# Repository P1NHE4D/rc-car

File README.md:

# RC Car Project
This repository contains all files for the controller boards I designed for a RC car I am building myself.

## Version 1
The first version of the board uses a AtMega 328 MCU for controlling the motor driver, lights, and steering of the car. It is connected to an external
ESP 8266 chip for enabling wireless communication.

<div align="center">

</div>

## Version 2
The second version is currently in development. It replaces the AtMega 328 chip with an on-board ESP32 in order to reduce the overall footprint
of the chip. It also features a USB-C connector to facilitate flashing and debugging the controller without having to rely on additional 
debugging equipment.

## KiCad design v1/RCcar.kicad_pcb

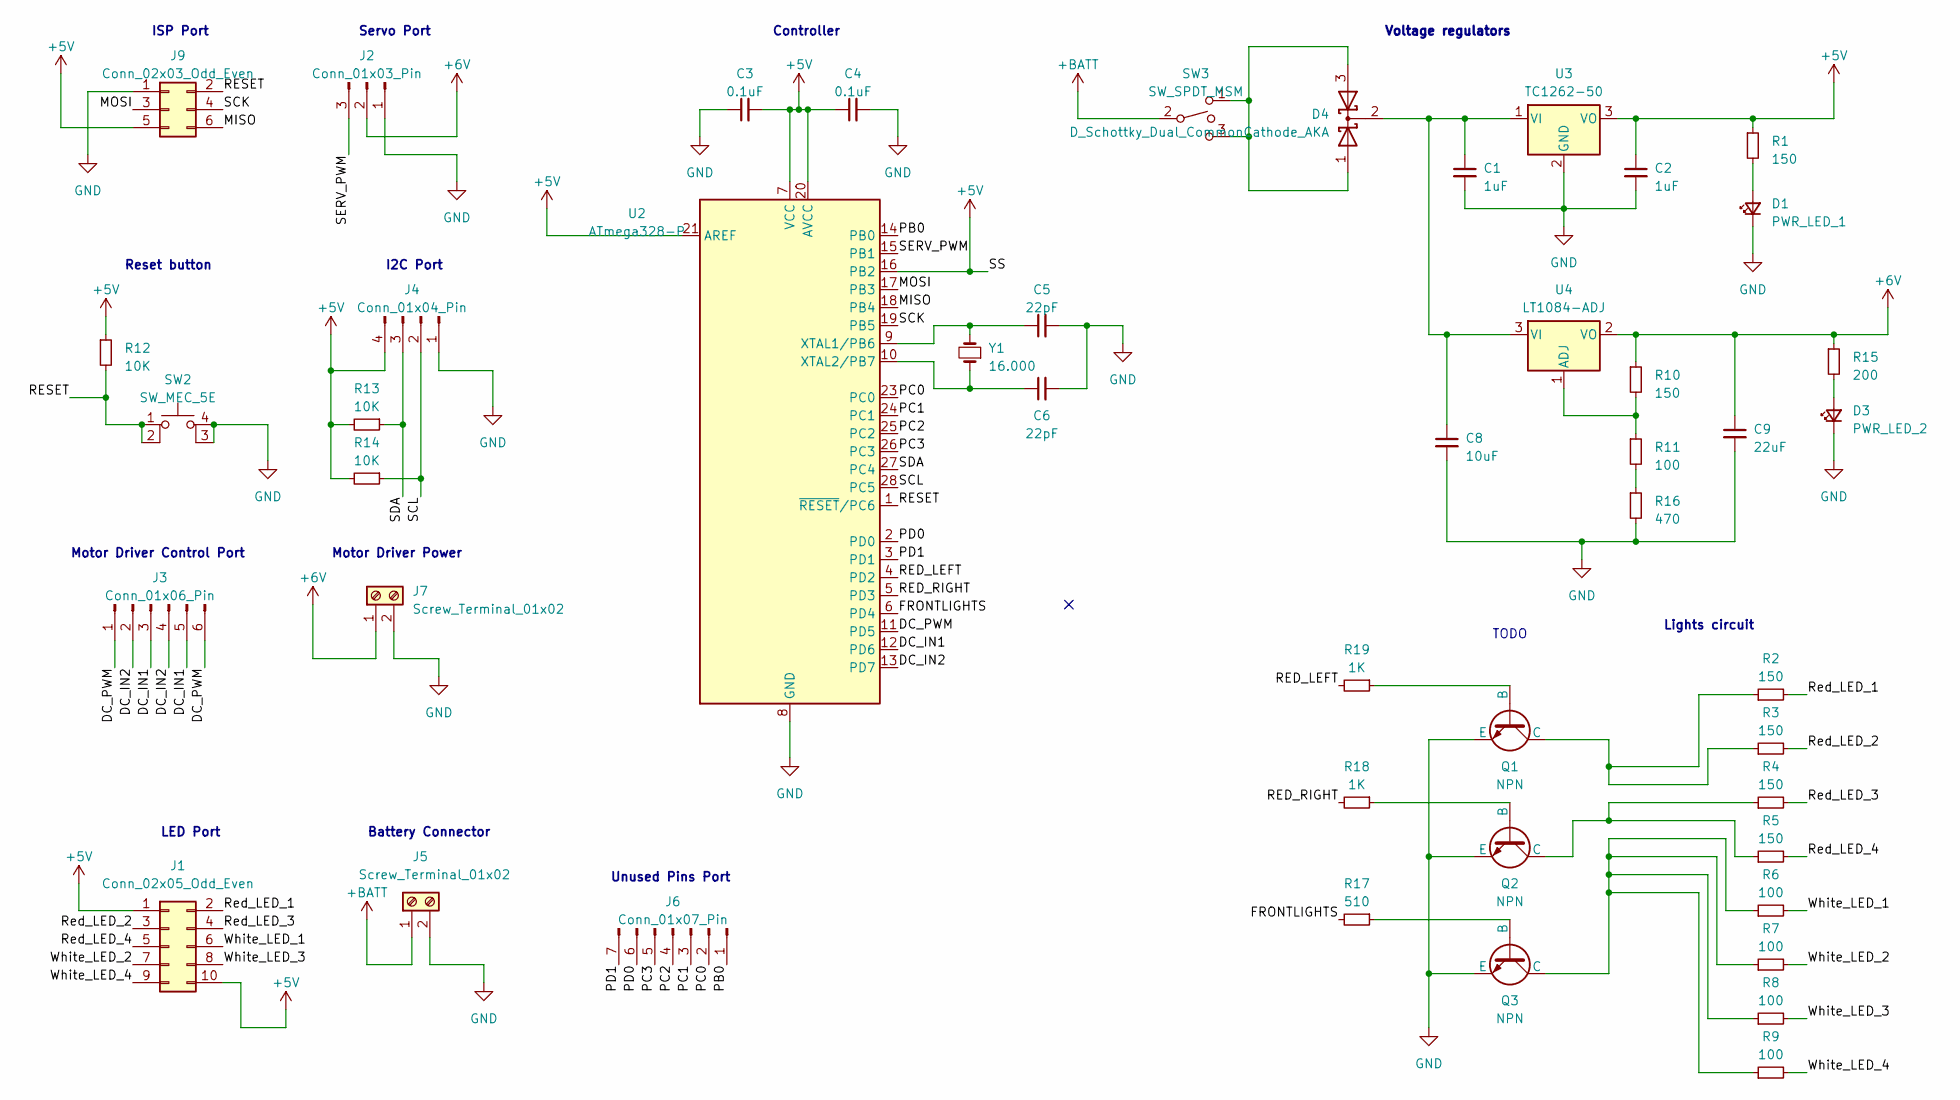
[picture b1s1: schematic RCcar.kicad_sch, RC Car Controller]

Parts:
C1, C2: 1uF; C_1206_3216Metric_Pad1.33x1.80mm_HandSolder
C3, C4: 0.1uF; C_1206_3216Metric_Pad1.33x1.80mm_HandSolder
C5, C6: 22pF; C_1206_3216Metric_Pad1.33x1.80mm_HandSolder
C8: 10uF; C_1206_3216Metric_Pad1.33x1.80mm_HandSolder
C9: 22uF; C_1206_3216Metric_Pad1.33x1.80mm_HandSolder
D1: PWR_LED_1; LED_1206_3216Metric_Pad1.42x1.75mm_HandSolder
D3: PWR_LED_2; LED_1206_3216Metric_Pad1.42x1.75mm_HandSolder
D4: D_Schottky_Dual_CommonCathode_AKA; TO-252-2
J1: Conn_02x05_Odd_Even; PinHeader_2x05_P2.54mm_Vertical
J2: Conn_01x03_Pin; PinHeader_1x03_P2.54mm_Vertical
J3: Conn_01x06_Pin; PinHeader_1x06_P2.54mm_Vertical
J4: Conn_01x04_Pin; PinHeader_1x04_P2.54mm_Vertical
J5, J7: Screw_Terminal_01x02; CTB0700-2
J6: Conn_01x07_Pin; PinHeader_1x07_P2.54mm_Vertical
J9: Conn_02x03_Odd_Even; PinHeader_2x03_P2.54mm_Vertical
Q1, Q2, Q3: NPN; SOT-23
R1, R2, R3, R4, R5, R10: 150; R_1206_3216Metric_Pad1.30x1.75mm_HandSolder
R6, R7, R8, R9, R11: 100; R_1206_3216Metric_Pad1.30x1.75mm_HandSolder
R12, R13, R14: 10K; R_1206_3216Metric_Pad1.30x1.75mm_HandSolder
R15: 200; R_1206_3216Metric_Pad1.30x1.75mm_HandSolder
R16: 470; R_1206_3216Metric_Pad1.30x1.75mm_HandSolder
R17: 510; R_1206_3216Metric_Pad1.30x1.75mm_HandSolder
R18, R19: 1K; R_1206_3216Metric_Pad1.30x1.75mm_HandSolder
SW2: SW_MEC_5E; ElegooButton
SW3: SW_SPDT_MSM; 1101M2S3CQE2
U2: ATmega328-P; DIP-28_W7.62mm
U3: TC1262-50; SOT-223
U4: LT1084-ADJ; TO-252-2
Y1: 16.000; Crystal_HC49-4H_Vertical

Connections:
+5V: C2.1, C3.2, C4.1, J1.1, J1.10, J4.4, J9.5, R1.1, R12.1, R13.2, R14.2, U2.7 (VCC), U2.16 (PB2), U2.20 (AVCC), U2.21 (AREF), U3.3 (VO)
+6V: C9.1, J2.2, J7.1, R10.1, R15.1, U4.2 (VO)
+BATT: J5.1, SW3.2
/DC_IN1: J3.3, J3.5, U2.12 (PD6)
/DC_IN2: J3.2, J3.4, U2.13 (PD7)
/DC_PWM: J3.1, J3.6, U2.11 (PD5)
/FRONTLIGHTS: R17.2, U2.6 (PD4)
/MISO: J9.6, U2.18 (PB4)
/MOSI: J9.3, U2.17 (PB3)
/PB0: J6.1, U2.14 (PB0)
/PC0: J6.2, U2.23 (PC0)
/PC1: J6.3, U2.24 (PC1)
/PC2: J6.4, U2.25 (PC2)
/PC3: J6.5, U2.26 (PC3)
/PD0: J6.6, U2.2 (PD0)
/PD1: J6.7, U2.3 (PD1)
/RED_LEFT: R19.2, U2.4 (PD2)
/RED_RIGHT: R18.2, U2.5 (PD3)
/RESET: J9.2, R12.2, SW2.1, SW2.2, U2.1 (~RESET/PC6)
/Red_LED_1: J1.2, R2.2
/Red_LED_2: J1.3, R3.2
/Red_LED_3: J1.4, R4.2
/Red_LED_4: J1.5, R5.2
/SCK: J9.4, U2.19 (PB5)
/SCL: J4.2, R14.1, U2.28 (PC5)
/SDA: J4.3, R13.1, U2.27 (PC4)
/SERV_PWM: J2.3, U2.15 (PB1)
/White_LED_1: J1.6, R6.2
/White_LED_2: J1.7, R7.2
/White_LED_3: J1.8, R8.2
/White_LED_4: J1.9, R9.2
GND: C1.2, C2.2, C3.1, C4.2, C5.2, C6.2, C8.2, C9.2, D1.1 (K), D3.1 (K), J2.1, J4.1, J5.2, J7.2, J9.1, Q1.3 (E), Q2.3 (E), Q3.3 (E), R16.2, SW2.3 (K), SW2.4 (A), U2.8 (GND), U2.22 (GND), U3.2 (GND)
unnamed: D1.2 (A), R1.2
unnamed: D3.2 (A), R15.2
unnamed: D4.1 (A), D4.3 (A), SW3.1, SW3.3
unnamed: C1.1, C8.1, D4.2 (K), U3.1 (VI), U4.3 (VI)
unnamed: Q1.2 (B), R19.1
unnamed: Q1.1 (C), R2.1, R3.1
unnamed: Q2.2 (B), R18.1
unnamed: Q2.1 (C), R4.1, R5.1
unnamed: Q3.2 (B), R17.1
unnamed: Q3.1 (C), R6.1, R7.1, R8.1, R9.1
unnamed: R11.2, R16.1
unnamed: C5.1, U2.9 (XTAL1/PB6), Y1.2
unnamed: C6.1, U2.10 (XTAL2/PB7), Y1.1
unnamed: R10.2, R11.1, U4.1 (ADJ)

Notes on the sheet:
Servo Port
LED Port
Voltage regulators
Reset button
Lights circuit
TODO
Battery Connector
Motor Driver Power
Controller
ISP Port
Motor Driver Control Port
I2C Port
Unused Pins Port

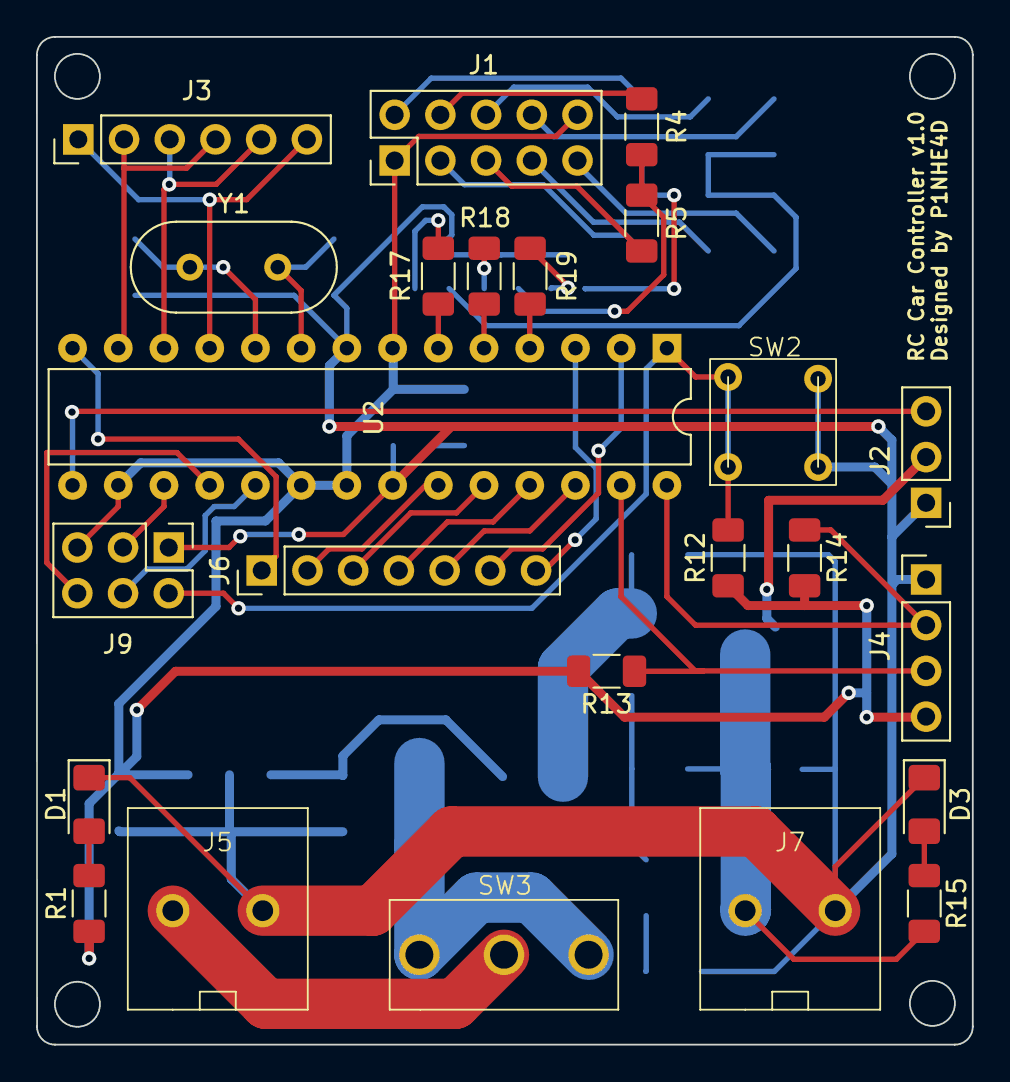
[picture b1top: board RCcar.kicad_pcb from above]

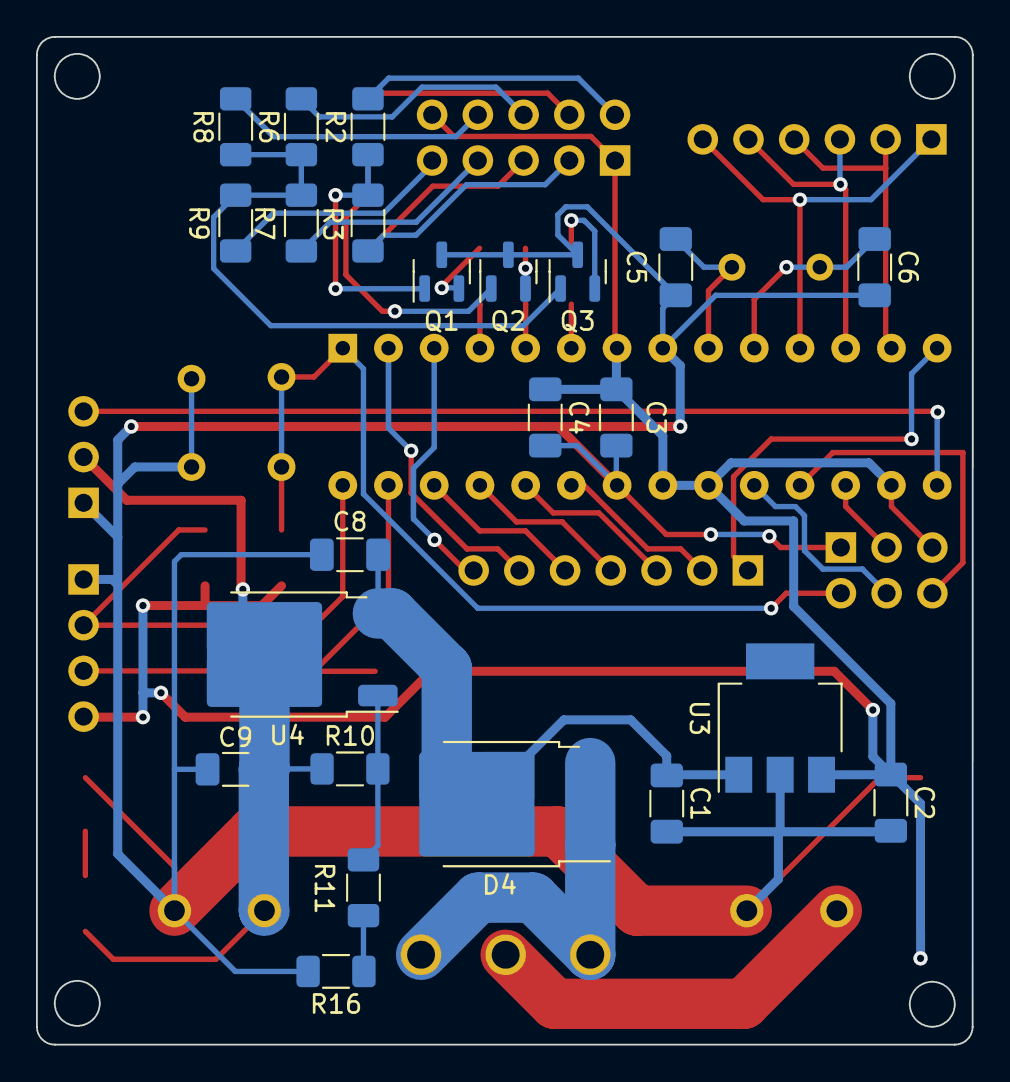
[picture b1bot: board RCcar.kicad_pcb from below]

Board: 2 copper layers, 52.0 x 56.0 mm, 47 parts (23 on the bottom side), 46 nets.

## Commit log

2023-07-23 add v1 files
2023-07-23 add subfolder
2023-07-23 move gitignore
2023-07-23 add v2 files
2023-07-23 add images
